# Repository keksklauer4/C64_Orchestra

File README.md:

# C64_Orchestra
A schematic and a pcb layout for a serial interface for C64 master-slave communication.

## This is a work in progress. I do not take any responsibility for what you do with this. Neither can I assure the correctness of anything that is stated here.
# Documentation
The board should be hooked directly to exactly 28 pins of the expansion port of the C64:
- D0-D7 as the data bus
- A0-A15 as the address bus
- Phi 2 (system clock, in schematics referred to as CPU_CLK)
- IRQ
- GND
- 5V DC

The board allows interfacing using several registers and may trigger an interrupt on the end of a transmitted packet. In order to send a packet, a developer first has to decide on who to send the packets to, sets 16 bit into specific registers, specifies whether an interrupt should be triggered on transmission end and then starts the transmission process.

For specifying the destination of a packet (each containing exactly 2 bytes), the board has two registers that can be written to (reading is not allowed). In sum, 16 destinations can be chosen in different combinations. Thus, up to 2^16 configurations are possible. The registers currently start at address 0xFFF8, which will change in the future (due to the fact that these addresses are used already). The destination register 1 (DEST1) lies at 0xFFF8, DEST2 (destination register 2) is located at 0xFFF9.

The packet to be send can then be written into two shift registers. Again, they are write-only due to the fact that there is no parallel-out on the chips used. The shift registers each contain 8 bit and are located at 0xFFFB (for SR1, holding the lower 8 bits) and 0xFFFC (for SR2, holding the upper 8 bits).

After the packet has been written to the shift registers, the developer has to decide on whether an Interrupt should be triggered on transmission end. Starting transmission and configuring whether triggering an interrupt is done in the same register. The WCR can be found at 0xFFFA. The least significant bit (at position 0) is a flag to set whether the transmission should start, a 1 denoting to start. The bit at position 1 denotes whether an interrupt should be triggered - a "1" indicates that an interrupt will be requested on transmission end.

As an alternative to using interrupts, the developer can initiate a read on the status register which is the WCR but read-only. The status register is located at address 0xFFFD. If the least significant bit is cleared, the transmission is done.

Since this board provides a master-slave hierarchy, the communication is unidirectional. No response is possible.

# How does it work until now?
It does not work. It is just a design. Apart from that, only the master board has been designed (it is much more complex) and a decision on the actual transmission has not been made yet (probably NRZ due to its simplicity).

## Now, how is it supposed to work (under the hood)?
That's how I like questions to be asked! Well, the schematics is split up into 6 parts:
- An Address resolver
- The destination control
- The transmitter circuit
- The status registers
- The circuit-internal clock circuit
- The outgate

It must be said that the latter two are *very* sparse and should not really be counted (but who cares?).

I will shortly explain the 6 parts.

### The outgate
As mentioned above, it is very simple because that is just an abstraction layer for the outputs of the circuit. The outputs are:
- 16 pin for destination control (each channel can be selected using one bit)
- 1 pin for the transmission clock (not the CPU clock)
- 1 pin for the actual signal send (serial signal)

For every C64 acting as a slave in the hierarchy another two chips are needed:
1. A chip to convert the signal and the clock of the master to the slave's power levels
2. A chip to read incoming serial data (potentially with error detection in the future), a binary counter to get that the transmission ended and a way to interface with the slave's expansion port (Interrupt and read control).

### The circuit-internal clock circuit
This part has not been designed yet (because it does not make sense to design that without testing the capabilities of a transmission).
The board should, however, have its own clock to allow for transmission frequencies below 1 MHz (otherwise errors might be too frequent). Either a LM555 or a crystal oscillator will be used. The internal clock circuit is only used in the outgate and the transmitter circuit.

### The address resolver
That part is rather simple (but will be adjusted to relocate the address the registers can be found at). Basically, two big AND gates (74HC30) check whether the upper 13 bit of the address lines (thus, pins A3-A15) are set to high. If that is the case, the multiplexer (74HC238) is enabled and evaluates the lower three bit. Depending on the output of the multiplexer, one of the registers is selected. These select lines are the outputs of the address resolver part. Let's shortly enumerate the different possibilities and the mapping to the select lines (a clever reader can predict the mapping by looking at the addresses of each register mentioned above):
A2-A1-A0
- 0-0-0 -> Destination register 1 (DEST1_Select)
- 0-0-1 -> Destination register 2 (DEST2_Select)
- 0-1-0 -> WCR (used to configure behavior on transmission end and to start transmitting)
- 0-1-1 -> SR1 (select line for the shift register 1)
- 1-0-0 -> SR2 (select line for the shift register 2)
- 1-0-1 -> Status register (read-only register to manually check the transmission status)
- 1-1-0 -> not in use
- 1-1-1 -> not in use

The beauty of the address resolver lies in the fact that no other part interfaces with the address bus (which reduces complexity).

The schematics for the address resolver is shown in the image below.

### The destination control
The destination control consists of two 8 bit registers (74HC374) to hold the destination configuration. Depending on the select lines of the address resolver, namely DEST1_Select and DEST2_Select, either destination register 1 or destination register 2 is written to, respectively. The ouputs of the destination registers are always fed directly to the outgate and are used to configure whether a slave should receive the packet or not.

The schematics (see the image below) are pretty straightforward:

### The status register
Internally, the status register consists of some combinational logic (that will be explained indirectly without going into too much depth), one 8-bit register (74HC374) that holds the data and two buffers to control the flow to the data bus of the C64. Apart from that, this part depends on the C64's clock (CPU Clock), two select lines of the address resolver, more precisely, for selecting WCR and selecting the status register, and a flag by the transmission circuit that tells whether a transmission has just ended.

Three different modes must be distinguished:
- Write to WCR: The data bus of the C64 contains the data to set the register to. Thus, the write buffer (bascially a tri-state gate) lets the data bus to the registers inputs and simulateously the load flag of the register is enabled.
- Read from status register: The output buffer (again a tri-state gate - a 74HC245) is set to let the data from the output of the register to the data bus and the output of the register is enabled while the input is disabled.
- Reset start flag: If a transmission has ended, the done flag will be HIGH. Then, the least significant bit of the status register should be cleared (set to LOW). To achieve that both buffers (the write and output buffer) are disabled, and the outputs of the status registers are tied to the input of the registers while the lowest bit is cleared. The load flag is set.

The status register is partially redundant and might be changed.

However, the schematics can be found in the image below. Do not try to understand it.

### The transmitter circuit
This is the heart of the whole board and therefore most of the complexity lies here. The transmitter circuit depends on the flags set in the status register, the C64's clock, the board's internal clock, the C64's data bus and the select lines for the registers SR1 and SR2 (the shift registers holding the packet data) by the address resolver. The outputs are the signal that will be fed to the outgate and the interrupt line.

The transmitter circuit consists of two shift registers (74LS165), a binary counter (74LS393) and quite some combinational logic. Depending on the current mode (transmission started or not) either the C64's clock (CPU_CLK) is fed to the shift registers or the board-internal clock (Own_CLK). If either of the select lines for the shift registers by the address resolver is HIGH, the respective shift register loads parallel from the data bus. Thus, if the transmission has started which is indicated through the status register's least significant bit, the board's internal clock will be fed to the currently needed shift register.

Determining which shift register is needed is achieved by checking the binary counter's most significant bit. If the most signficant bit is not set, SR1 (shift register 1) is shifted and the output is fed out to the outgate as SIGNAL. Otherwise, SR2 is shifted an its output is taken. The binary counter starts counting when transmission starts and indirectly counts the bits transmitted. Thus, if the most significant bit is set that is equivalent to "at least 8 bits have been transmitted" which in turn means SR1 is empty (which is why SR2 is taken).

The binary counter is reset (set to 0) when transmission ends. Whenever the binary counter reaches 15, the transmission has ended (16 bit have been transmitted), the output flag that indicates the end of a transmission is set to HIGH (which triggers a clear in the status register part). If the status register is set to trigger an interrupt on transmission end, an interrupt is requested on transmission end.

In the future, depending on the quality of this work, maybe a waitstate is inserted every 8 bit to add a parity bit (to allow for error detection at the slave).

# ICs required (until now)

## Usual logic gate types:
- [74HC04](https://github.com/keksklauer4/C64_Orchestra/blob/master/docs/74LS04.pdf) (NOT gates)
- [74HC08](https://github.com/keksklauer4/C64_Orchestra/blob/master/docs/74LS08.pdf) (2-input AND)
- [74LS21](https://github.com/keksklauer4/C64_Orchestra/blob/master/docs/74LS21.pdf) (4-input AND)
- [74HC30](https://github.com/keksklauer4/C64_Orchestra/blob/master/docs/74LS30.pdf) (8-input NAND)
- [74HC32](https://github.com/keksklauer4/C64_Orchestra/blob/master/docs/74LS32.pdf) (2-input OR)

## Registers:
- [74LS165](https://github.com/keksklauer4/C64_Orchestra/blob/master/docs/74LS165.pdf) (parallel in, serial out shift register; 8 bit)
- [74HC173](https://github.com/keksklauer4/C64_Orchestra/blob/master/docs/74LS173.pdf) (4 bit register)
- [74HC374](https://github.com/keksklauer4/C64_Orchestra/blob/master/docs/74LS374.pdf) (8 bit register)

## Misc:
- [74HC237](https://github.com/keksklauer4/C64_Orchestra/blob/master/docs/74HC237.pdf) (3 bit multiplexer)
- [74HC245](https://github.com/keksklauer4/C64_Orchestra/blob/master/docs/74LS245.pdf) (tri-state buffer)
- [74HC393](https://github.com/keksklauer4/C64_Orchestra/blob/master/docs/74LS393.PDF) (binary counter)

## Probably added in the future:
- Some oscillator (around 1 MHz)
- [6n137](https://github.com/keksklauer4/C64_Orchestra/blob/master/docs/6n137.pdf) (highspeed optocoupler)

## Probably solely for the receiver:
- [74HC595]() (parallel out, serial in shift register; 8 bit)

Note that the ICs of the 74LS and 74HC series cannot be randomly interchanged. The output of a 74LS cannot drive an input of a 74HC due to a difference in the voltage level for a logic HIGH. In order to drive an input of a 74HC using a 74LS's output, one should (or must) use pull-up resistor of at least 600 ohm. The ohmage could be different depending on one's power supply.

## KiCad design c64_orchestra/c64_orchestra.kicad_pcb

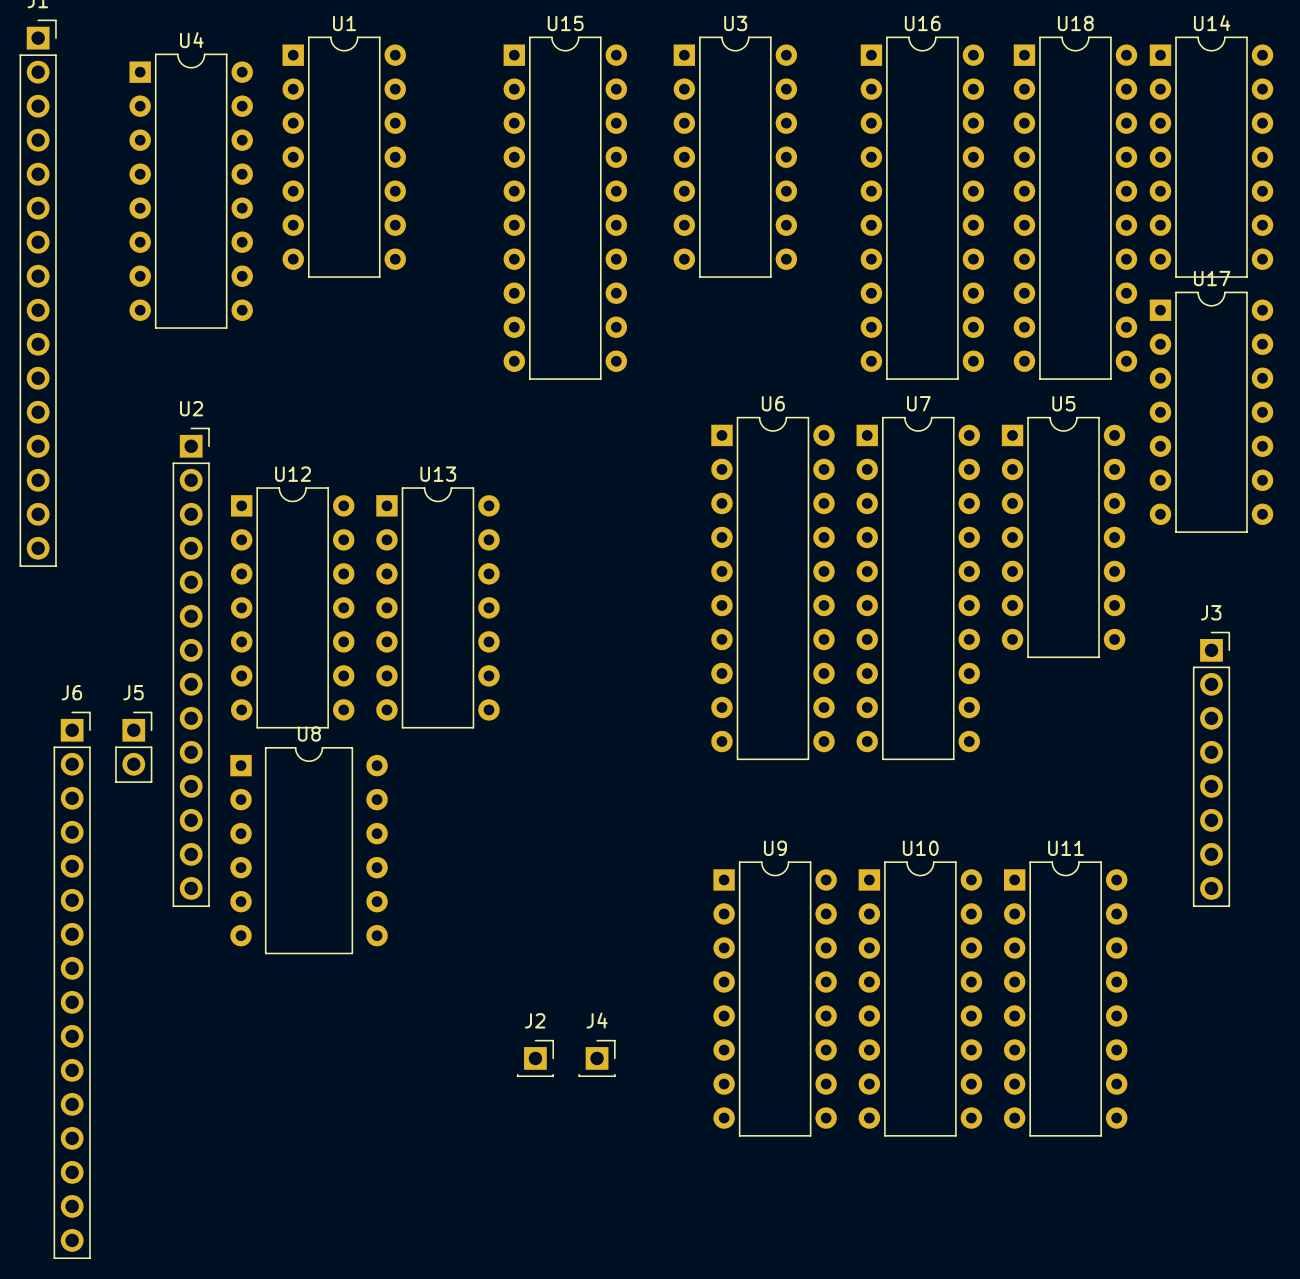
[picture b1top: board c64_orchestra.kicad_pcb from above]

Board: 2 copper layers, 24 parts (0 on the bottom side), 90 nets, no tracks yet.

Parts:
J1: Conn_01x16; PinSocket_1x16_P2.54mm_Vertical
J2, J4: Conn_01x01; PinSocket_1x01_P2.54mm_Vertical
J3: Conn_01x08; PinSocket_1x08_P2.54mm_Vertical
J5: Conn_01x02_Male; PinSocket_1x02_P2.54mm_Vertical
J6: Conn_01x16_Male; PinSocket_1x16_P2.54mm_Vertical
U1: 7430; DIP-14_W7.62mm
U2: 7430; PinSocket_1x14_P2.54mm_Vertical
U3, U17: 7432; DIP-14_W7.62mm
U4: 74HC237; DIP-16_W7.62mm
U5, U12: 7408; DIP-14_W7.62mm
U6, U7, U18: 74HC374; DIP-20_W7.62mm
U8: 7404; DIP-12_W10.16mm
U9, U10: 74165; DIP-16_W7.62mm
U11: 74LS393; DIP-16_W7.62mm
U13: 7421; DIP-14_W7.62mm
U14: 7402; DIP-14_W7.62mm
U15, U16: 74HC245; DIP-20_W7.62mm

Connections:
/adress_resolver/A0: J1.1, U4.1
/adress_resolver/A1: J1.2, U4.2
/adress_resolver/A2: J1.3, U4.3
/adress_resolver/A3: J1.4, U2.5
/adress_resolver/A4: J1.5, U2.4
/adress_resolver/A5: J1.6, U2.3
/adress_resolver/A6: J1.7, U2.2
/adress_resolver/A7: J1.8, U2.1
/adress_resolver/A8: J1.9, U1.12
/adress_resolver/A9: J1.10, U1.11
/adress_resolver/A10: J1.11, U1.6
/adress_resolver/A11: J1.12, U1.5
/adress_resolver/A12: J1.13, U1.4
/adress_resolver/A13: J1.14, U1.3
/adress_resolver/A14: J1.15, U1.2
/adress_resolver/A15: J1.16, U1.1
/adress_resolver/Dest1: U4.15, U5.1
/adress_resolver/Dest2: U4.14, U5.4
/adress_resolver/SR1: U4.12, U8.1
/adress_resolver/SR2: U4.11, U8.3
/destination_control/CPU_CLK: J2.1, U5.2, U5.5, U5.10, U12.13
/destination_control/IO0: J3.1, U6.3, U7.3, U9.11, U10.11, U15.2, U16.2
/destination_control/IO1: J3.2, U6.4, U7.4, U9.12, U10.12, U15.3, U16.3
/destination_control/IO2: J3.3, U6.7, U7.7, U9.13, U10.13, U15.4, U16.4
/destination_control/IO3: J3.4, U6.8, U7.8, U9.14, U10.14, U15.5, U16.5
/destination_control/IO4: J3.5, U6.13, U7.13, U9.3, U10.3, U15.6, U16.6
/destination_control/IO5: J3.6, U6.14, U7.14, U9.4, U10.4, U15.7, U16.7
/destination_control/IO6: J3.7, U6.17, U7.17, U9.5, U10.5, U15.8, U16.8
/destination_control/IO7: J3.8, U6.18, U7.18, U9.6, U10.6, U15.9, U16.9
/outgate/Signal: J5.1, U3.8
/status_registers/ETransmit: U5.13, U8.5, U16.18, U18.2
/status_registers/Select_Status: U3.13, U4.10, U14.3
/status_registers/Select_WCR: U4.13, U8.11
/status_registers/Trigger_INT_Flag: U12.10, U15.17, U16.17, U18.4, U18.5
/transmitter/Done: U3.12, U12.9, U13.6, U14.2
/transmitter/IRRequest: J4.1, U12.8
Dest0: J6.1, U6.2
Dest1: J6.2, U6.5
Dest2: J6.3, U6.6
Dest3: J6.4, U6.9
Dest4: J6.5, U6.12
Dest5: J6.6, U6.15
Dest6: J6.7, U6.16
Dest7: J6.8, U6.19
Dest8: J6.9, U7.2
Dest9: J6.10, U7.5
Dest10: J6.11, U7.6
Dest11: J6.12, U7.9
Dest12: J6.13, U7.12
Dest13: J6.14, U7.15
Dest14: J6.15, U7.16
Dest15: J6.16, U7.19
Global_GND: U4.5, U4.8, U6.1, U6.10, U7.1, U7.10, U9.8, U10.8, U14.7, U15.10, U16.1, U16.10, U17.1, U18.10
Global_VCC: U2.6, U2.11, U2.12, U4.6, U6.20, U7.20, U15.1, U15.20, U16.20, U18.20
Gnd: U1.7, U1.14, U2.7, U2.14, U3.7, U3.14, U5.7, U5.14, U8.7, U12.7, U12.14, U13.7, U13.14, U17.7, U17.14
unnamed: U1.8, U3.1
unnamed: U2.8, U3.2
unnamed: U3.3, U4.4
unnamed: U5.3, U6.11
unnamed: U5.6, U7.11
unnamed: U5.9, U8.6
unnamed: U8.2, U9.1
unnamed: U8.4, U10.1
unnamed: U10.2, U12.3
unnamed: U3.10, U10.9
unnamed: U3.4, U5.8, U11.1
unnamed: U3.5, U5.11, U11.2
unnamed: U11.3, U13.1
unnamed: U11.4, U13.2
unnamed: U11.5, U13.4
unnamed: U11.6, U13.5
unnamed: U3.6, U12.1, U12.4
unnamed: U8.9, U12.2
unnamed: U8.8, U12.5
unnamed: U9.2, U12.6
unnamed: U12.11, U18.11
unnamed: U3.11, U12.12
unnamed: U14.1, U18.1
unnamed: U15.11, U16.11, U18.18, U18.19
unnamed: U15.12, U16.12, U18.16, U18.17
unnamed: U15.13, U16.13, U18.14, U18.15
unnamed: U15.14, U16.14, U18.12, U18.13
unnamed: U15.15, U16.15, U18.8, U18.9
unnamed: U15.16, U16.16, U18.6, U18.7
unnamed: U15.18, U17.2
unnamed: U8.10, U15.19
unnamed: U8.12, U16.19
unnamed: U17.3, U18.3
Own_CLK: J5.2, U5.12
VCC: U4.16, U9.16, U10.16, U14.14

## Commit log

2020-10-16 Initial commit. Added parts of schematic.
2020-10-16 Added some useful documents.
2020-10-16 Added list of parts needed
    List of parts is not finished yet (because the schematics is not done yet).
2020-10-16 Added documents.
2020-10-16 Added parts of schematic and worked on pcb layout.
2020-10-21 Changed the logic gates' numbering, changed some gates for todos.
2020-10-21 Added images, changed readme.
2020-10-21 Fixed typos
2020-10-28 Started implementing hamming code on 6502.
